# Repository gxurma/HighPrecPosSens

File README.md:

# HighPrecPosSens

High precision Position Sensor System using
* Hamamatsu s12443, 
* a gradient lens array,
* a paper or metal stripe / code encoder scale 
* an RP2040 or Teensy 4.1 µC board.

## s12443

Pixel size: 7 x 125 μm, 2496 pixels, small package

The S12443 is a CMOS linear image sensor with a compact yet 2496-pixel long photosensitive area (effective photosensitive area length: 17.472 mm). The pixel size is 7 x 125 μm.

* Features
* Pixel size: 7 × 125 μm
* 2496 pixels
* Effective photosensitive area length: 17.472 mm
* 3.3 V single power supply operation
* Built-in timing generator allows operation with only Start and Clock pulse inputs
* Video data rate: 10 MHz max.
* Small imput terminal capacitance: 5 pF

In my experiments I saw that 10MHz usage is leading to higher noise levels.

I recommend 5 MHz pxel clock signal, thats nicely representing the measured analog signal.

## Credits to

https://github.com/ncarandini/KiCad-RP-Pico.git

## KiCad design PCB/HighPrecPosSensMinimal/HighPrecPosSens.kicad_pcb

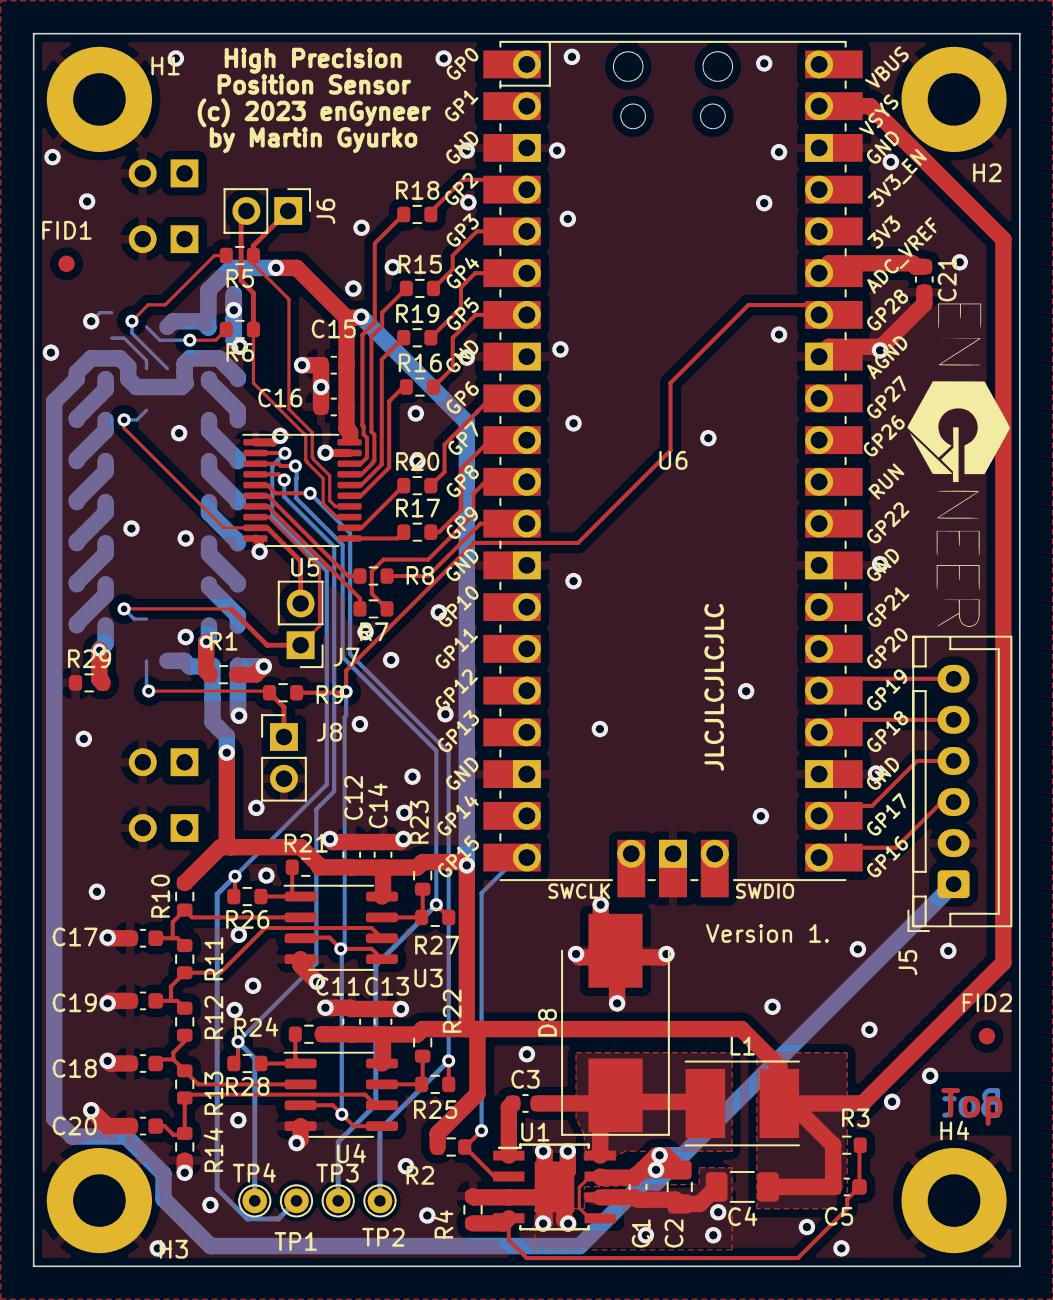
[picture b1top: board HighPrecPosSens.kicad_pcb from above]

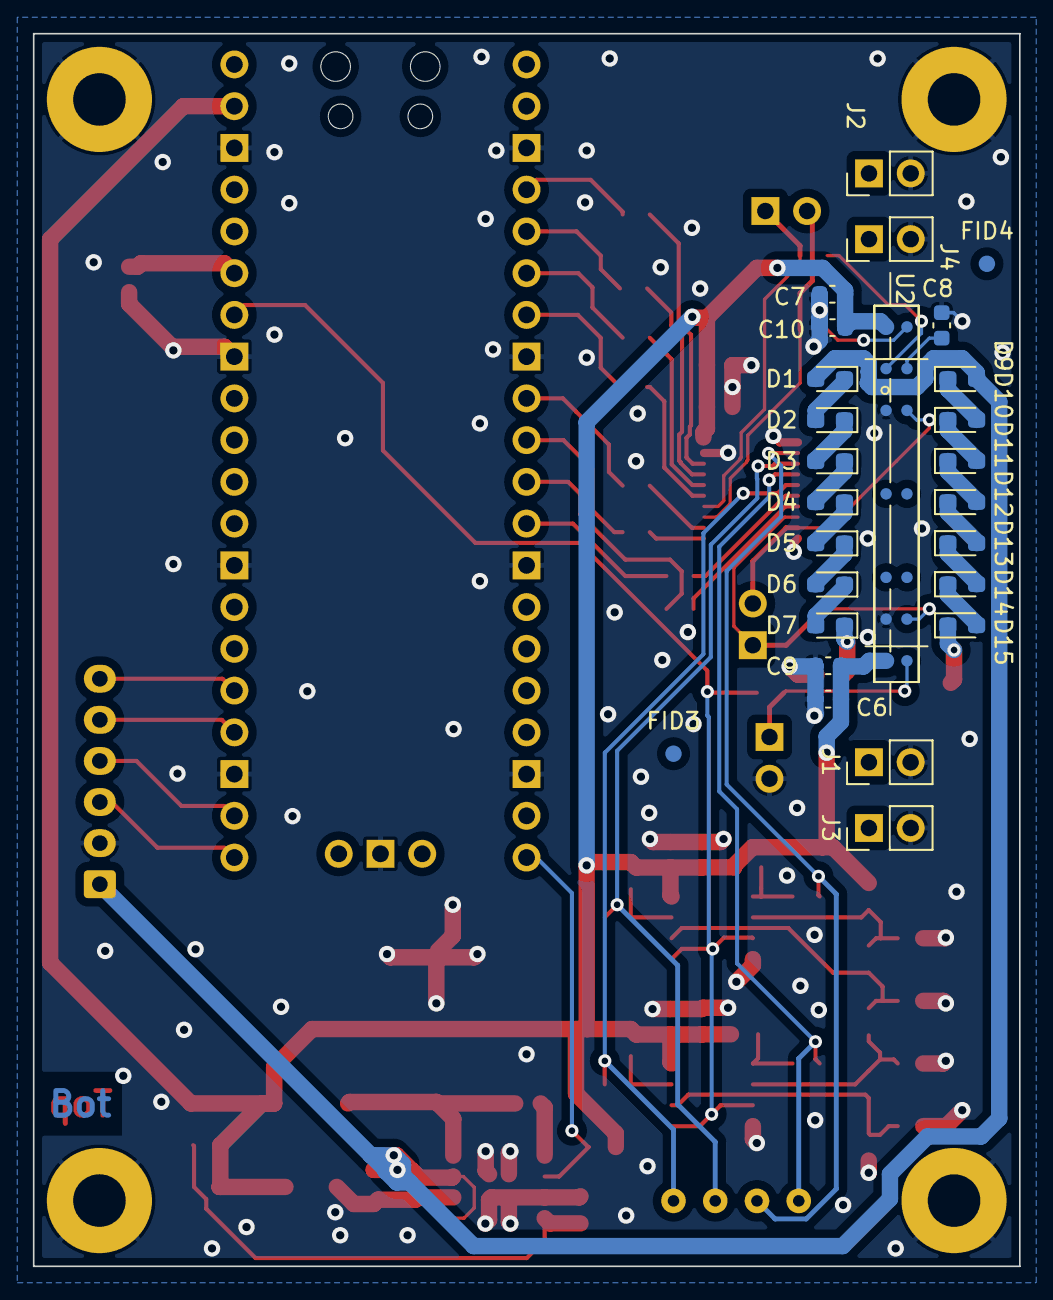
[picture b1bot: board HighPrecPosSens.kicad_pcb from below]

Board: 2 copper layers, 60.0 x 75.0 mm, 93 parts (26 on the bottom side), 63 nets.

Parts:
C1, C3, C9, C10, C13, C14, C16, C21: 100n; C_0603_1608Metric
C2: 10u; C_0805_2012Metric_Pad1.18x1.45mm_HandSolder
C4: 100u; C_1206_3216Metric_Pad1.33x1.80mm_HandSolder
C5: 150p; C_0603_1608Metric
C6, C7, C11, C12, C15: 22u; C_0603_1608Metric
C8, C17, C18, C19, C20: 1u; C_0603_1608Metric
D1, D2, D3, D4, D5, D6, D7, D9, D10, D11, D12, D13, D14, D15: LED; LED_0603_1608Metric_Pad1.05x0.95mm_HandSolder
D8: SS36; D_SMC_Handsoldering
FID1, FID2, FID3, FID4: Fiducial; Fiducial_1mm_Mask2mm
G1: LOGO; enGyneer-Logo
H1, H2, H3, H4: MountingHole_Pad; MountingHole_3.2mm_M3_Pad
J1, J2, J3, J4, J6, J7, J8: Conn_01x02_Male; PinHeader_1x02_P2.54mm_Vertical
J5: Conn_01x06_Male; JST_XH_B6B-XH-A_1x06_P2.50mm_Vertical
L1: 10u; L_Taiyo-Yuden_NR-50xx_HandSoldering
R1, R5, R6, R7, R8, R15, R16, R17, R18, R19, R20, R25, R26, R27, R28, R29: 82; R_0603_1608Metric
R2: 47k; R_0603_1608Metric
R3: 4.7k; R_0603_1608Metric
R4: 2.7k; R_0603_1608Metric
R9: 100; R_0603_1608Metric
R10: 3.6k; R_0603_1608Metric
R11, R12, R13, R21, R22, R23, R24: 1k; R_0603_1608Metric
R14: 4.3k; R_0603_1608Metric
TP1, TP2, TP3, TP4: TestPoint; TestPoint_THTPad_D1.5mm_Drill0.7mm
U1: ST1S14PHR; TI_SO-PowerPAD-8
U2: S12443; s12443
U3, U4: LM393DR2G; SOIC-8_3.9x4.9mm_P1.27mm
U5: 74LVC541A; TSSOP-20_4.4x6.5mm_P0.65mm
U6: Pico; RPi_Pico_SMD_TH

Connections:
+3.3V: C4.1, C5.1, C6.1, C7.1, C9.1, C10.1, C11.1, C12.1, C13.1, C14.1, C15.1, C16.1, L1.2, R2.1, R3.2, R10.2, R21.2, R22.2, R23.2, R24.2, U2.1 (Vdd), U2.7 (Vdd), U3.8 (V+), U4.8 (V+), U5.20 (VCC), U6.39 (VSYS)
+24V: C1.1, C2.1, D1.2 (A), D9.2 (A), J5.1, U1.5 (EN2), U1.7 (VIN)
/Boot: C3.1, U1.1 (BOOT)
/CLk: J6.1, R5.1, U5.14 (Y4)
/Clk_2: R5.2, U2.2 (Clk)
/D1: R25.2, TP2.1, U5.5 (A3)
/D2: R28.2, TP4.1, U5.4 (A2)
/D3: R27.2, TP3.1, U5.3 (A1)
/D4: R26.2, TP1.1, U5.2 (A0)
/EOS: J7.1, U2.9 (EOS), U5.8 (A6)
/FB: C5.2, R3.1, R4.2, U1.4 (FB)
/ST: J6.2, R6.1, U5.13 (Y5)
/ST_2: R6.2, U2.14 (ST)
/Switch: C3.2, D8.1 (K), L1.1, U1.8 (SW)
/Trig: J7.2, U2.12 (Trig), U5.9 (A7)
/V1: C20.1, R13.1, R14.2, U4.6 (-)
/V2: C18.1, R12.1, R13.2, U4.2 (-)
/V3: C19.1, R11.1, R12.2, U3.6 (-)
/V4: C17.1, R10.1, R11.2, U3.2 (-)
/Video: J8.1, R9.1, U2.8 (Video)
/Video1: R9.2, U3.3 (+), U3.5 (+), U4.3 (+), U4.5 (+), U6.34 (GPIO28_ADC2)
GND: C1.2, C2.2, C4.2, C6.2, C7.2, C8.2, C9.2, C10.2, C11.2, C12.2, C13.2, C14.2, C15.2, C16.2, C17.2, C18.2, C19.2, C20.2, C21.2, D8.2 (A), H1.1, H2.1, H3.1, H4.1, J1.2, J2.2, J3.2, J4.2, J5.2, J8.2, R1.1, R4.1, R14.1, R29.1, U1.3 (~EN1), U1.6 (GND), U1.9 (PADGND), U2.3 (Vss), U2.6 (Vss), U3.4 (V-), U4.4 (V-), U5.1 (G1), U5.10 (GND), U5.19 (G2), U6.3 (GND), U6.8 (GND), U6.13 (GND), U6.18 (GND), U6.23 (GND), U6.28 (GND), U6.33 (AGND), U6.38 (GND), U6.42 (GND)
Miso: J5.3, U6.21 (GPIO16)
Mosi: J5.6, U6.25 (GPIO19)
unnamed: C8.1, U2.13 (Vcp)
unnamed: C21.1, U6.35 (ADC_VREF)
unnamed: D1.1 (K), D2.2 (A)
unnamed: D2.1 (K), D3.2 (A)
unnamed: D3.1 (K), D4.2 (A)
unnamed: D4.1 (K), D5.2 (A)
unnamed: D5.1 (K), D6.2 (A)
unnamed: D6.1 (K), D7.2 (A)
unnamed: D7.1 (K), R1.2
unnamed: D10.1 (K), D11.2 (A)
unnamed: D9.1 (K), D10.2 (A)
unnamed: D11.1 (K), D12.2 (A)
unnamed: D12.1 (K), D13.2 (A)
unnamed: D13.1 (K), D14.2 (A)
unnamed: D14.1 (K), D15.2 (A)
unnamed: D15.1 (K), R29.2
unnamed: R7.1, U6.11 (GPIO8)
unnamed: R7.2, U5.7 (A5)
unnamed: R8.1, U6.12 (GPIO9)
unnamed: R8.2, U5.6 (A4)
unnamed: R15.1, U5.17 (Y1)
unnamed: R15.2, U6.5 (GPIO3)
unnamed: R16.1, U5.15 (Y3)
unnamed: R16.2, U6.7 (GPIO5)
unnamed: R17.1, U5.11 (Y7)
unnamed: R17.2, U6.10 (GPIO7)
unnamed: R18.1, U5.18 (Y0)
unnamed: R18.2, U6.4 (GPIO2)
unnamed: R19.1, U5.16 (Y2)
unnamed: R19.2, U6.6 (GPIO4)
unnamed: R20.1, U5.12 (Y6)
unnamed: R20.2, U6.9 (GPIO6)
unnamed: R21.1, R26.1, U3.1
unnamed: R22.1, R25.1, U4.7
unnamed: R23.1, R27.1, U3.7
unnamed: R24.1, R28.1, U4.1
PGood: R2.2, U1.2 (PG), U6.20 (GPIO15)
SCS: J5.4, U6.22 (GPIO17)
SCkl: J5.5, U6.24 (GPIO18)

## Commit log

2022-09-30 added datasheet
2022-11-13 first measurement data for analysis and optimization
2022-11-13 renamed test to Test and added csv usage to gitignore
2022-11-14 added flowcsv project
2022-11-14 added long movement run, high res
2022-11-27 added pdf of sensor
2023-02-10 Added Hamamatsu Sensor SE CAD files
2023-02-10 First commit of kicad design
2023-02-10 removed unnecessary folder pdf
2023-02-10 moved CAD data to CAD
2023-02-10 added firmware dir
2023-02-10 Valami leiras
2023-02-10 tidy up docs
2023-02-10 Finished 3d model of sensor
2023-02-12 added symbol of s12443
2023-02-13 added some parts to it
2023-02-14 Added 2 bit ADC
2023-02-15 Added 2 bit ADC ladder and comparators
2023-02-15 added some wires and simulation of lt1818
2023-02-17 added pico to schematic
2023-02-18 added credit to https://github.com/ncarandini/KiCad-RP-Pico.git
2023-02-23 added some power supply
2023-02-24 added some pullups and positioned power supply better
2023-02-25 First netlist transfer
2023-02-26 Some layouting
2023-02-26 simulation of lm393
2023-02-26 layouting
2023-02-27 Added some missing parts and more LEDs
2023-02-27 Routed layout
2023-02-27 some mounting holes added
2023-02-27 Some readibility and overlap issues fixed, added some more ground vias
2023-02-27 Added some text
2023-02-28 Added some mounting or not definitions
2023-03-03 Added some reasonable testpoints
2023-03-03 Added logo
2023-03-03 moved logo
2023-03-03 changed vias
2023-03-06 Some minor changes
2023-03-09 moved stuff
2023-03-10 some minor attribute changes
2023-03-10 Produktionsfiles
2023-03-10 moved back footpronts and symbols for reuse
2023-03-12 added simper sensor layout
2023-03-19 Just breaking my head with current layout
2023-04-21 added first testFW
2023-04-22 nur zum Test
2023-04-23 now i can change on the fly the frq and duty
2023-04-24 10MHz seems to work OK. Now able to play with speed and duty cycle.
2023-04-29 PWM mag keine 2 Cores Nach der ersten Sekunde bleibt PWM stehen...
2023-05-15 compiling and working code. still massive timing ans readout issues.
2023-05-15 Somewhat working condition, but data readout does not give synchronized data. Something is really wrong.
2023-05-18 bissl gehts, aber muss noch dran gefeilt werden
2023-05-22 found out that 250k is better...
2023-05-22 last ino to get something going on the arduino dev. ide
2023-05-22 Blockdiagramm added
2023-05-24 Added real first readout. Triggered by serial comm over USB
2023-05-24 added serial readout python progi
2023-05-24 somewhat working readout
2023-05-26 Now synchronisation works perfectly.
2023-05-27 nice visualisation
2023-05-30 Erste gescheite Ergebnisse
2023-05-30 Erste Python Positionsergebnisse
2023-05-31 Using phase correlation
2023-05-31 Neuer, saubererer Barcode macht erste Positionsanzeige möglich
2023-06-12 Needed some example barcode stripes
2023-06-23 Added some design rules
2023-06-26 trying out new scale
2023-07-18 added laser diode pdf
2023-10-01 for better scales we use de bruijn
2023-10-01 made it easier to use
2023-10-02 genauestes ergebnis mit delta berechnung
2023-10-03 Added 3d models
2023-10-13 Paar Aufnahmen zum üben mit Matlab

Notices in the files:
PCB/HighPrecPosSensMinimal/HighPrecPosSens.kicad_pcb:
(c) 2023 enGyneer
